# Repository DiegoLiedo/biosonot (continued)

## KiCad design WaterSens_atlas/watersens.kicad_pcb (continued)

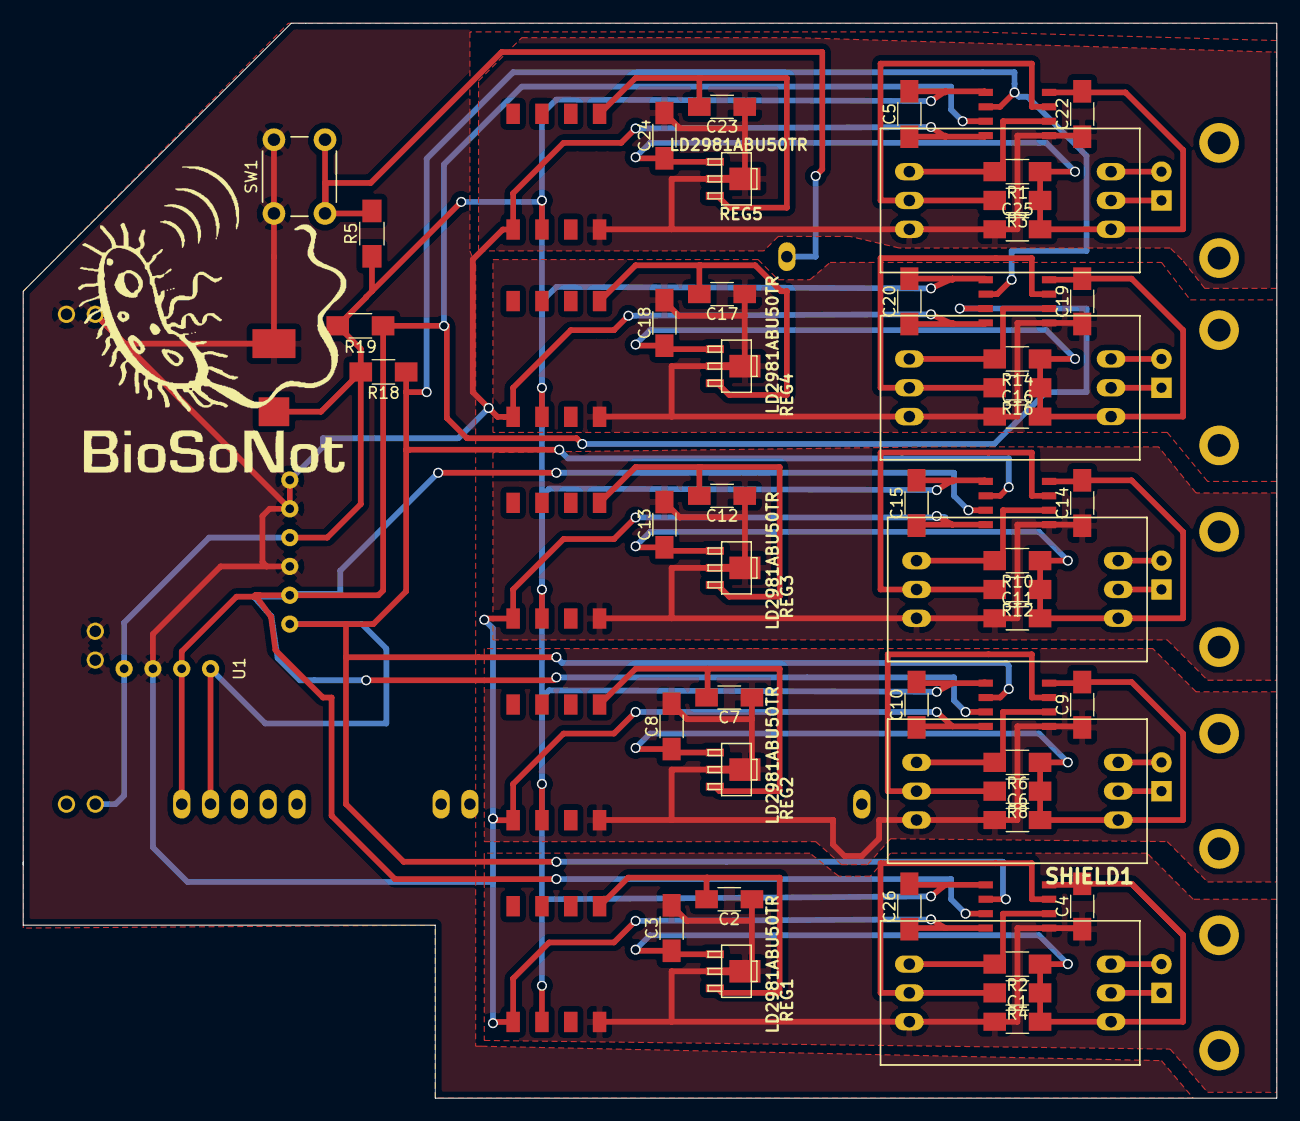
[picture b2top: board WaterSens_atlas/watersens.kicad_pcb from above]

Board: 2 copper layers, 110.5 x 94.7 mm, 67 parts (0 on the bottom side), 40 nets.
